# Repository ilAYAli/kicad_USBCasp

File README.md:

# USBCasp

Compact USB-C AVR programmer based on the classic USBasp design and an `ATmega8`.

### PCB

### Finished product

## Hardware

This project is a USBasp-compatible AVR ISP programmer with:

- `ATmega8-16AU`
- `12 MHz` external crystal
- USB-C connector with USB 2.0 data pair
- 2x5 ICSP header for programming target AVRs

The USBasp firmware in this repo is configured for:

- `D- = PB0`
- `D+ = PB1`
- `D+` also tied to `PD2 / INT0`
- `12 MHz` clock

### Firmare

```sh
git clone https://github.com/Ser9ei/usbasp.git
```

## Programming One USBasp From Another

If you already have one working USBasp, you can use it to program another `ATmega8` USBasp target over the ICSP header.
If the board does not enumerate as USBasp yet, replace `-c usbasp` with your external programmer, for example `-c avrisp2`.

Set `SPRG` on the target board to `ON`, connect the two boards through the 2x5 ISP header, then run:

### Program using a pre-programmed USBasp

```sh
avrdude -c usbasp -p m8 -B 10 -U hfuse:w:0xc9:m -U lfuse:w:0xef:m
avrdude -c usbasp -p m8 -B 10 -e -U ./firmware/usbasp/firmware/usbasp_atmega8_2026-04-12.hex:i
```

### Program using an avrisp2

```sh
avrdude -c avrisp2 -p m8 -B 10 -U hfuse:w:0xc9:m -U lfuse:w:0xef:m
avrdude -c avrisp2 -p m8 -B 10 -e -U ./firmware/usbasp/firmware/usbasp_atmega8_2026-04-12.hex:i
```

### Verify the firmware (connect the newly programmed USBCasp)

```sh
avrdude -c usbasp -p m8 -n -v
```

### Then verify real ISP communication against a known-good target AVR:

```sh
avrdude -c usbasp -p m8 -B 32 -v
```

Or for a different target, for example `ATtiny84`:

```sh
avrdude -c usbasp -p t84 -B 32 -v
```

## Repo Layout

- [USBCasp.kicad_sch](USBCasp.kicad_sch) and [USBCasp.kicad_pcb](USBCasp.kicad_pcb): hardware design
- [firmware/usbasp/firmware](https://github.com/Ser9ei/usbasp.git): USBasp firmware source and build artifacts
- [firmware/FLASH_AND_TEST.md](firmware/FLASH_AND_TEST.md): extra flashing and bring-up notes

## Original implementation

https://www.fischl.de/usbasp/

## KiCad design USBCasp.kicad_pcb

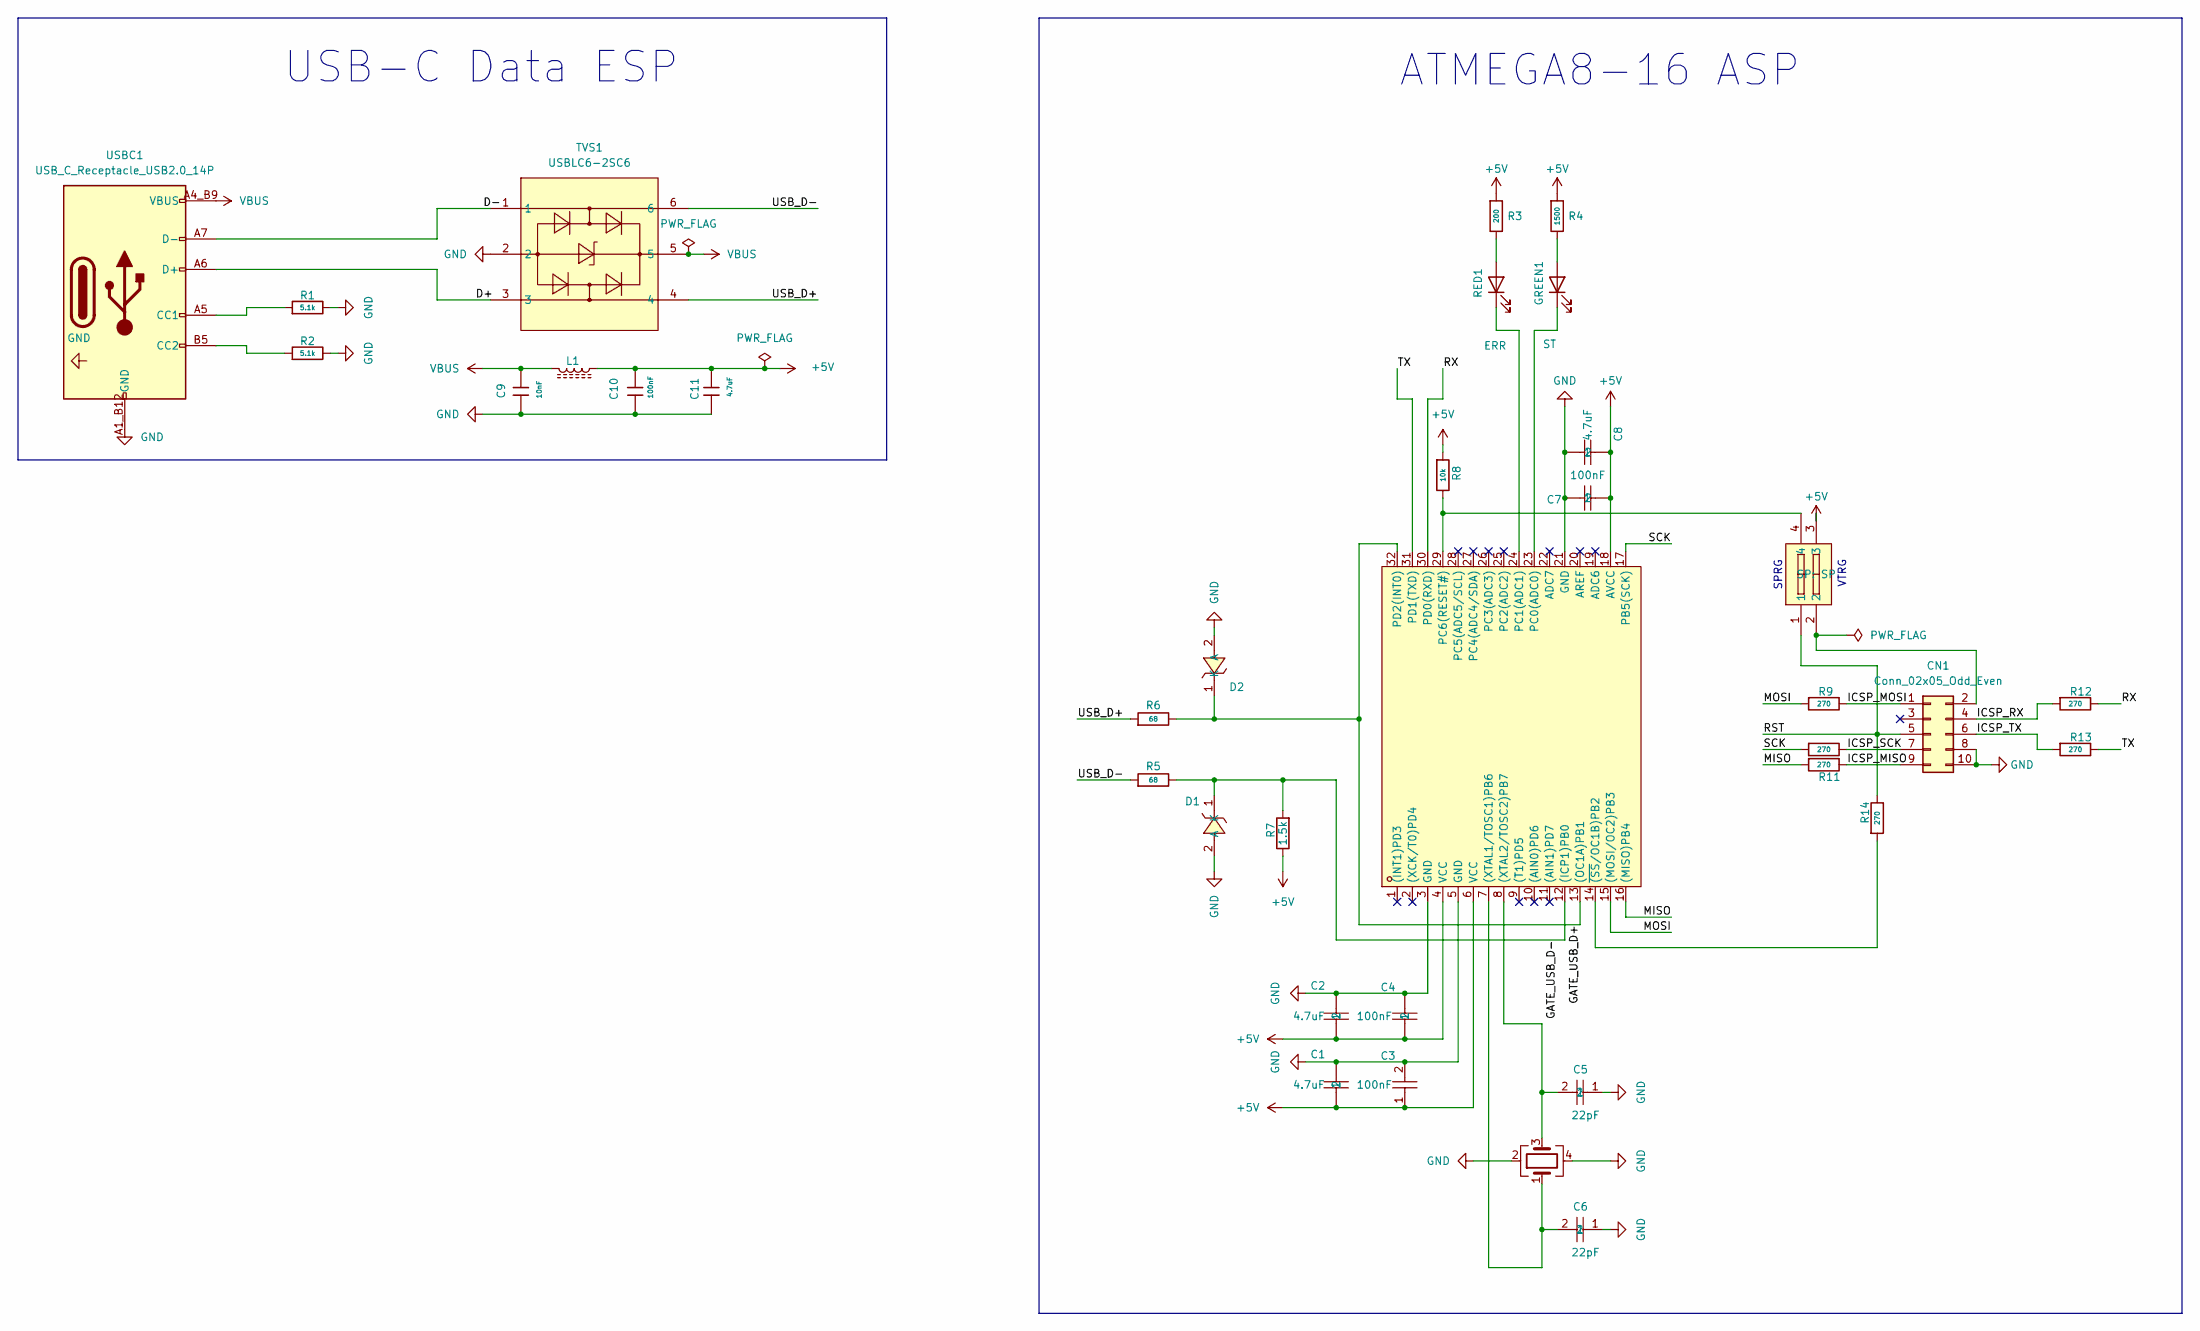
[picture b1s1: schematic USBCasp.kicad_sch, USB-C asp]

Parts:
C1, C2, C8: 4.7uF; C_0805_2012Metric; Part CL21A475KBQNNNE; LCSC Part C98192
C3, C4: 100nF; C_0805_2012Metric; Part CC0805KRX7R9BB104; LCSC Part C49678
C5, C6: 22pF; C_0805_2012Metric; Part CL21C220JBANNNC; LCSC Part C1804
C7: 100nF; R_0805_2012Metric; Part CC0805KRX7R9BB104; LCSC Part C49678
C9: 10nF; C_0805_2012Metric; Part CC0805KRX7R9BB103; LCSC C83170
C10: 100nF; C_0805_2012Metric; LCSC C49678
C11: 4.7uF; C_0805_2012Metric; Part GRM21BZ71H475KE15L; LCSC C437557
CN1: Conn_02x05_Odd_Even; IDC-Header_2x05_P2.54mm_Vertical
D1, D2: BZT52C3V6_C19077397; D_SOD-123; LCSC Part C19077397
GREEN1: ST; LED_0805_2012Metric; Mfr. Part NCD0805G1; LCSC Part C8426
L1: 600; L_0805_2012Metric; Mrf part MPZ2012S601AT000; LCSC Part C21519
R1, R2: 5.1k; R_0805_2012Metric; Part 0805W8F5101T5E; LCSC C27834
R3: 200; R_0805_2012Metric; Part FRC0805F2000TS; LCSC C2907239
R4: 1500; R_0805_2012Metric; Mfr. Part RC0805FR-071K5L; LCSC C114555
R5, R6: 68; R_0805_2012Metric; Part 0805W8F680JT5E; LCSC C17802
R7: 1.5k; R_0805_2012Metric; Part 0805W8F3600T5E; LCSC Part C114555
R8: 10k; R_0805_2012Metric; Part RC0805FR-0710KL; LCSC C84376
R9, R10, R11, R12, R13, R14: 270; R_0805_2012Metric; Part RC0805FR-07270RL; LCSC Part C137558
RED1: ERR; LED_0805_2012Metric; Mfr. Part YLED0805R; LCSC Part C19171391
TVS1: USBLC6-2SC6; SOT-23-6; LCSC Part C7519
U1: ATMEGA8-16AU; TQFP-32_7x7mm_P0.8mm; LCSC Part C1337807
U2: SMXS-02K-TP; SW-SMD_SMXS-02K-TP; LCSC Part 2
USBC1: USB_C_Receptacle_USB2.0_14P; USB-C_Receptacle
X1: 12Mhz; Crystal_SMD_3225-4Pin_3.2x2.5mm; Part X322512MSB4SI; LCSC C9002

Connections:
+5V: C1.1, C2.1, C3.1, C4.1, C7.2, C8.2, C10.1, C11.1, L1.1, R3.1, R4.1, R7.2, R8.1, U1.4 (VCC), U1.6 (VCC), U1.18 (AVCC), U2.3
/D+: TVS1.3, USBC1.A6 (D+), USBC1.B6 (D+)
/D-: TVS1.1, USBC1.A7 (D-), USBC1.B7 (D-)
/GATE_USB_D+: D2.1 (K), R6.2, U1.13 ((OC1A)PB1), U1.32 (PD2(INT0))
/GATE_USB_D-: D1.1 (K), R5.2, R7.1, U1.12 ((ICP1)PB0)
/ICSP_MISO: CN1.9, R11.1
/ICSP_MOSI: CN1.1, R9.1
/ICSP_RX: CN1.4, R12.2
/ICSP_SCK: CN1.7, R10.1
/ICSP_TX: CN1.6, R13.2
/MISO: R11.2, U1.16 ((MISO)PB4)
/MOSI: R9.2, U1.15 ((MOSI/OC2)PB3)
/RST: CN1.5, R14.1, U2.1
/RX: R12.1, U1.30 (PD0(RXD))
/SCK: R10.2, U1.17 (PB5(SCK))
/TX: R13.1, U1.31 (PD1(TXD))
/USB_D+: R6.1, TVS1.4
/USB_D-: R5.1, TVS1.6
GND: C1.2, C2.2, C3.2, C4.2, C5.1, C6.1, C7.1, C8.1, C9.2, C10.2, C11.2, CN1.8, CN1.10, D1.2 (A), D2.2 (A), R1.2, R2.2, TVS1.2, U1.3 (GND), U1.5 (GND), U1.21 (GND), USBC1.1, USBC1.2, USBC1.3, USBC1.4, USBC1.A1_B12 (GND), USBC1.B1_A12 (GND), X1.2, X1.4
unnamed: CN1.2, U2.2
unnamed: GREEN1.2 (A), R4.2
unnamed: GREEN1.1 (K), U1.23 (PC0(ADC0))
unnamed: R3.2, RED1.2 (A)
unnamed: RED1.1 (K), U1.24 (PC1(ADC1))
unnamed: C6.2, U1.7 ((XTAL1/TOSC1)PB6), X1.1
unnamed: C5.2, U1.8 ((XTAL2/TOSC2)PB7), X1.3
unnamed: R8.2, U1.29 (PC6(RESET#)), U2.4
unnamed: R14.2, U1.14 (~(SS/OC1B)PB2)
unnamed: R1.1, USBC1.A5 (CC1)
unnamed: R2.1, USBC1.B5 (CC2)
VBUS: C9.1, L1.2, TVS1.5, USBC1.A4_B9 (VBUS), USBC1.B4_A9 (VBUS)

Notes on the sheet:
SPRG
VTRG
ATMEGA8-16 ASP
USB-C Data ESP

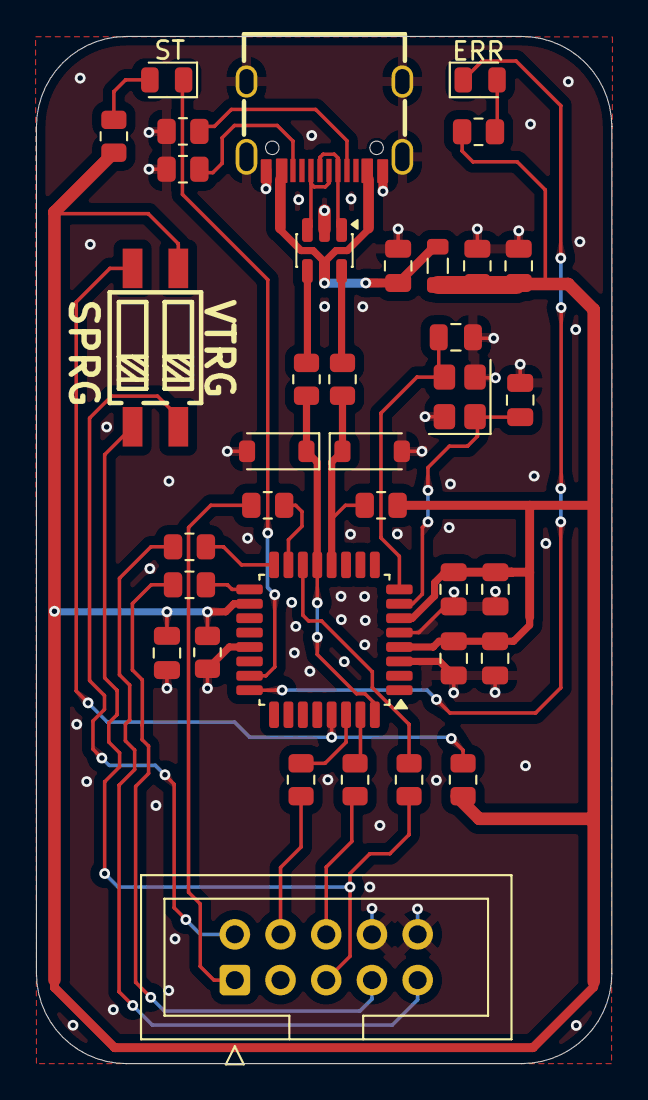
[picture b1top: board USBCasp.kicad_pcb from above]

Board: 2 copper layers, 32.0 x 57.1 mm, 36 parts (0 on the bottom side), 31 nets.

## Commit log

2026-04-15 initial
2026-04-29 update README.md with USBasp firmware link
